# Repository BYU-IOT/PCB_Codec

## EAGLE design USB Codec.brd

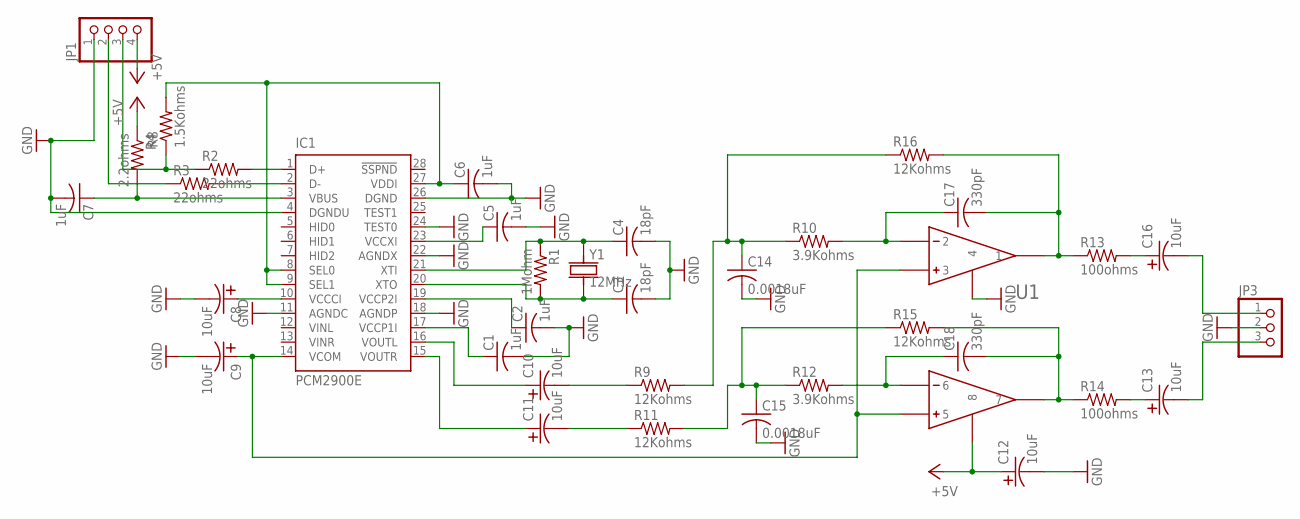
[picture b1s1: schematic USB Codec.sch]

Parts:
C1, C2, C5, C6, C7: 1uF; 0603_CAP
C3, C4: 18pF; 0603_CAP
C8, C9, C10, C11, C12, C13, C16: 10uF; 1411_CAP
C14, C15: 0.0018uF; 0603_CAP
C17, C18: 330pF; 0603_CAP
IC1: PCM2900E; SSOP28DB
JP1: PINHD-1X4; 1X04
JP3: PINHD-1X3; 1X03
R1: 1Mohm; 0603_RESISTOR
R2, R3: 22ohms; 0603_RESISTOR
R4: 2.2ohms; 0603_RESISTOR
R8: 1.5Kohms; 0603_RESISTOR
R9, R11, R15, R16: 12Kohms; 0603_RESISTOR
R10, R12: 3.9Kohms; 0603_RESISTOR
R13, R14: 100ohms; 0603_RESISTOR
U1: OP-AMP; OPA2353UA
Y1: 12MHz; CRYSTAL_5X3

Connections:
+5V: C12.P$1, JP1.4, R4.1, U1.P$8 (8)
GND: C1.2, C2.2, C3.2, C4.2, C5.2, C6.2, C7.2, C8.P$2, C9.P$2, C12.P$2, C14.2, C15.2, IC1.4 (DGNDU), IC1.11 (AGNDC), IC1.18 (AGNDP), IC1.22 (AGNDX), IC1.24 (TEST0), IC1.26 (DGND), JP1.1, JP3.2, U1.P$4 (4)
unnamed: C1.1, IC1.17 (VCCP1I)
unnamed: IC1.1 (D+), R2.2
unnamed: JP1.3, R2.1, R8.1
unnamed: C6.1, IC1.8 (SEL0), IC1.9 (SEL1), IC1.27 (VDDI), R8.2
unnamed: IC1.2 (D-), R3.2
unnamed: JP1.2, R3.1
unnamed: C5.1, IC1.23 (VCCXI)
unnamed: C10.P$2, R9.1
unnamed: C2.1, IC1.19 (VCCP2I)
unnamed: C11.P$2, R11.1
unnamed: C4.1, IC1.21 (XTI), R1.1, Y1.1
unnamed: C3.1, IC1.20 (XTO), R1.2, Y1.2
unnamed: C17.1, R10.2, U1.P$2 (2)
unnamed: C18.1, R12.2, U1.P$6 (6)
unnamed: C7.1, IC1.3 (VBUS), R4.2
unnamed: C8.P$1, IC1.10 (VCCCI)
unnamed: C9.P$1, IC1.14 (VCOM), U1.P$3 (3), U1.P$5 (5)
unnamed: C14.1, R9.2, R10.1, R16.1
unnamed: C10.P$1, IC1.16 (VOUTL)
unnamed: C11.P$1, IC1.15 (VOUTR)
unnamed: C15.1, R11.2, R12.1, R15.1
unnamed: C17.2, R13.1, R16.2, U1.P$1 (1)
unnamed: C16.P$2, JP3.1
unnamed: C18.2, R14.1, R15.2, U1.P$7 (7)
unnamed: C13.P$2, JP3.3
unnamed: C16.P$1, R13.2
unnamed: C13.P$1, R14.2

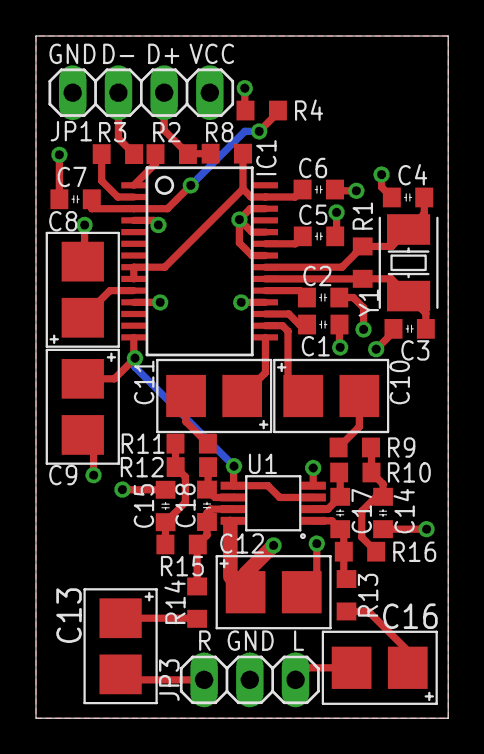
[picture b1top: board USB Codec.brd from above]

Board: 4 copper layers, 22.9 x 37.9 mm, 36 parts (0 on the bottom side), 29 nets.

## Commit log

2017-05-13 A test design PCB to test out the audio CODEC
    This repository contains the eagle files for the audio CODEC. The
    gerber files and PDFs of the schematic and layout. It doesn’t contain a
    bill of material. However in the PCB_Doorbell_coordinator there is a
    bill of material and this circuit is incorporated into the doorbell
    coordinator.
